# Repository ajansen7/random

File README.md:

# Random Scripts Repository

A collection of various scripts, experiments, and miscellaneous code.

## Projects

### 🧮 Aspens Calculator (`aspens-calculator/`)
- **Purpose**: Computer vision scripts likely for tile or board analysis.
- **Key Tools**: `opencv-python`, `numpy`.
- **Contents**: 
  - Several versions of a calculator (`calc_v*.py`)
  - `training.py` and `training-v2.py` for model training/data collection.
  - `tile-finder.py` for image analysis.

### 🦕 Dino Gen (`dino-gen/`)
- **Purpose**: QR code stitching and image processing, including a Streamlit app.
- **Key Tools**: `streamlit`, `opencv-python`, `pyzbar`.
- **Contents**:
  - `dino_app.py`: Streamlit-based application.
  - `qr_auto_stitch.py`, `qr_manual.py`, `qr_sticter.py`: Tools for QR code processing.

### 🍎 New Fruit (`new-fruit/`)
- **Purpose**: A static web page showcasing fruit/meat hybrids.
- **Key Tools**: HTML, CSS, assets (images and audio).
- **Contents**:
  - `index.html`: The main page.
  - Various image assets like `apple_steak.png` and `banana_sausage.png`.

### 📞 Tattle Phone (`tattle-phone/`)
- **Purpose**: A 3D-printed, toddler-proof 90s-style handset that records "tattles" and uploads them to Google Drive.
- **Key Tools**: ESP32-S3 (Arduino), custom KiCad PCB, Google Apps Script.
- **Contents**:
  - `README.md`: Full design doc (architecture, BOM, power, PCB, enclosure, build plan).
  - `firmware/tattle_phone/`: Record/upload firmware.
  - `cloud/drive_upload.gs`: Drive upload receiver with email notification.

## Setup

### Python Dependencies
To install the necessary Python libraries:

```bash
pip install -r requirements.txt
```

Note: `pyzbar` may require additional system-level libraries (e.g., `libzbar-dev` on Linux or `zbar` via Homebrew on macOS).

## Contributing
Feel free to add your own random scripts or improve existing ones!

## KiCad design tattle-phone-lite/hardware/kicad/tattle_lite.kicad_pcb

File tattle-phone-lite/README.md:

# Tattle Phone Lite

A much cheaper version of [`../tattle-phone`](../tattle-phone): **3 big buttons, 3×AA batteries,
a 2-layer board with every factory part on one side.** Same idea: a toddler presses a button,
it records what they say and sends it to a parent (Google Drive + email), and two phones can
call each other on the home Wi-Fi.

| | Original | Lite |
|---|---|---|
| Buttons | 12-key keypad + CALL | ⭐ TATTLE (yellow star), 🟢 CALL / ANSWER (green circle), 🔴 HANG UP (red square) |
| Lights | 14 smart RGB LEDs | 6 plain LEDs (two per button, matching colours), shining up through holes in the board |
| Power | Li-ion + charger + fuel gauge + buck-boost | 3×AA (alkaline or NiMH) + one 3.3 V regulator; battery level from a resistor divider |
| Board | 4 layers, parts on both sides | 2 layers, factory parts on the back only; you solder the 3 buttons and a few wires |
| Parts per board | ≈ $23 | ≈ $7 |
| Case | 175 × 52–58 × 30 mm | 170 × 60–62 × 34.5 mm, battery door with one screw |

## Status

1. ✅ Parts chosen and checked against JLC stock and datasheets (list below).
2. ✅ Board + case geometry (`hardware/layout.py`), case model (`enclosure/`), STLs build.
3. ✅ KiCad board: 54.4 × 120.5 mm, 2 layers, routed, **DRC 0 errors / 0 unconnected**,
   schematic and board match on all 164 pins. Fab files with a full LCSC BOM in `hardware/fab/`.
4. ✅ Firmware written and **compiles cleanly** (ESP32 core 3.3.12, 0 warnings with `-Wall`). Not yet run on hardware.

## Parts (factory-placed, all on the back)

| Ref | Part | LCSC | Notes |
|---|---|---|---|
| U1 | ESP32-S3-WROOM-1-N8R2 | C2913204 | S3, not C3: the C3 can't decode a PDM mic in hardware and has only one I2S |
| MK1 | LinkMems LMD3526B261-OFA03 | C41347997 | PDM, **bottom port** over a hole in the board. Pins: 1 DATA, 2 L/R, 3 CLK, 4 VDD, 5 GND ring. Do not wash |
| U2 | MAX98357A | C910544 | speaker amp, runs from the batteries |
| U3 | RT9080-33GJ5 | C841192 | 3.3 V LDO, 2 µA idle; same pinout as AP2112K |
| Q1 | AO3401A | C15127 | reverse-battery protection |
| SW4 | Shouhan MSK12C02 | C431540 | power switch, drives the LDO's EN pin only (it's a 50 mA switch) |
| J1 | HRO TYPE-C-31-M-12 | C165948 | **programming only**, no power path: batteries must be in to flash |
| LED1–6 | Lite-On LTST-C230 reverse-mount (yellow C125108, green C125106, red C125107) | | lens fits KiCad's `LED_1206_3216Metric_ReverseMount_Hole1.8x2.4mm` |

**You buy and solder:** see **[SHOPPING.md](SHOPPING.md)** for every part number, the LCSC
order file, the mechanical bits and a from-scratch tool list. The case is sized for a
**Keystone 2465** 3×AA holder (58 × 48.3 × 17 mm); for another holder, measure it and edit
`BATT_HOLDER` in `hardware/layout.py`.

## Case

`enclosure/tattle_lite.scad` (open in OpenSCAD, F5). `cd enclosure && make` builds `stl/` and
`pcb_outline.dxf`; `make renders` makes the pictures in `renders/`.

- **Battery door:** the holder sticks to the inside of the door (foam tape or screws). Undo
  one screw, lift door + holder out on the leads, swap cells. The far end hooks under the back
  wall. A screwed door is the norm for toys for under-3s.
- **Power switch** is recessed in the right side: a fingernail or pen tip moves it, a toddler
  mostly can't.
- **Buttons:** print the caps in translucent filament in each colour. A flange under the
  front wall keeps each one captive once the case is closed.

## Board (`hardware/`)

Everything is generated from two files: `hardware/layout.py` (positions shared with the case)
and `hardware/kicad_gen/design.py` (every part and what each pin connects to).

```
hardware/kicad_gen/run_all.sh     # build -> route -> stitch -> check -> make_fab
```

| Script | Does |
|---|---|
| `build.py` | schematic + placed, unrouted board; writes the mic footprint (from its datasheet), a reverse-mount LED footprint with a slightly smaller lens hole, and a DRC rule for those holes |
| `route.py` | FreeRouting (Java 25 + `~/tools/freerouting/freerouting-2.4.1.jar`). GND is left to the pours; the pours' "plane" blocks are stripped from the DSN so FreeRouting doesn't see a board-sized obstacle. Locked items (the amp's thermal-pad via) are kept |
| `stitch.py` | GND stitching vias on a 4 mm grid wherever both layers have pour, then one via per leftover pour island. Run **once** after `route.py` |
| `check.py` | schematic-vs-board netlist check + grouped DRC |
| `make_fab.py` | Gerbers + drill zip, `bom_jlc.csv` (LCSC numbers from `lcsc.py`), `cpl_jlc.csv` |

`run_all.sh` overwrites the board. Once you've hand-edited it in KiCad, run only `check.py`
and `make_fab.py`. FreeRouting isn't deterministic, so each full run gives slightly different
traces; the checks are what matter.

**Ordering (JLCPCB):** 2 layers, 1.6 mm, 54.4 × 120.5 mm. Min via **0.3 mm** (every hole is
≥ 0.3 mm: KiCad's ESP32 footprint has 0.2 mm thermal vias, which `build.py` re-drills to 0.3 mm,
because 0.2 mm holes move a 2-layer board into a much pricier class). Via covering: **Plugged**
for factory assembly (there's a via in the amp's thermal pad and 12 in the ESP32's ground pad);
**Tented** (or Untented) is fine if you assemble it yourself; see the note on via-in-pad below.
**Assembly: bottom side only.** Upload `hardware/fab/tattle_lite_gerbers.zip`, then
`bom_jlc.csv` + `cpl_jlc.csv`. In the placement preview check the LEDs, U1–U3, Q1 and the mic.
Board options: no washing / no conformal coating (MEMS mic).

**Expected DRC warnings:** "footprint doesn't match library" for the generated/locked
footprints, and two small silkscreen overlaps.

**Assembling it yourself:** stencil + paste + hotplate for the back (one pass), then the three
buttons by hand (clip the leads flush). Hard parts: the mic (no leads, keep paste and air out of
its port, never wash), the amp (3×3 mm QFN), the ESP32's ground pad, USB-C. Vias inside pads
(ESP32 ground pad, amp thermal pad) wick a little solder unless the vias are plugged: use a
touch more paste there or Kapton tape over them on the far side. First power-up from a
current-limited bench supply (~4.5 V, 200 mA) after checking 3V3 and VBAT aren't shorted to GND.

## Firmware (`firmware/tattle_lite/`)

**What the buttons do**

| Button | Idle | Ringing (incoming) | In a call |
|---|---|---|---|
| ⭐ yellow star | record a tattle (beep, talk, it stops on silence or another press) and send it to Drive + email | | |
| 🟢 green circle | call the other phone | answer | (nothing: just talk) |
| 🔴 red square | show battery (3/2/1 red blinks) and go to sleep | decline | hang up (either phone) |

Lights: the button you're using glows (yellow follows your voice while recording; green
follows the other kid's voice in a call). A faint green "breath" when idle means the
phone is on Wi-Fi and can be called.

**Power:** deep sleep until a button is pressed. After any use the phone stays awake
and callable for `AWAKE_MINUTES` (default 5). Optional `PLAY_START_HOUR`/`PLAY_END_HOUR`
keep both phones callable all afternoon (they also wake themselves at the start time),
at the cost of battery: roughly 20-30 mA while awake.

**Calls:** both phones must be on the same Wi-Fi. They find each other by name with
UDP broadcasts (no IP addresses to configure); `INTERCOM_KEY` must match on both. If
your router has "client/AP isolation" (common on guest networks), turn it off for this
network. If the other phone is asleep, the caller hears a descending "sleepy" tune.
Calls are **full duplex** like a real phone: both kids can talk at once. Each phone runs
Espressif's acoustic echo canceller (ESP-SR, built into the ESP32-S3 core) so its own
earpiece isn't sent back to the other kid as an echo. If a call still echoes or howls
after tuning, `#define CALL_MODE_WALKIE` in `config.h` switches to walkie-talkie calls
(hold green to talk); the firmware also falls back to that by itself if the echo
canceller can't start.

**Set up and flash**

1. Deploy `cloud/drive_upload.gs` as a Google Apps Script web app (steps in its header).
2. `cp firmware/tattle_lite/config.example.h firmware/tattle_lite/config.h` and fill in
   Wi-Fi, the upload URL/token, and the two phone names (swapped on the other phone).
3. Batteries in, power ON, USB-C cable to the computer, then
   `firmware/build.sh /dev/cu.usbmodem*` (find the port with `arduino-cli board list`).
   Arduino IDE instead: board "ESP32S3 Dev Module", Flash Size 8MB, PSRAM "QSPI PSRAM",
   Partition Scheme "Custom" (uses `partitions.csv`), USB CDC On Boot "Enabled".
4. If it won't flash: hold 🟢 green while switching on (that's the BOOT strap), flash,
   switch off and on.

**First bring-up, and tuning** (serial monitor at 115200 shows what's happening):
- Recording: `rms=` lines show the mic level. Talking should be well above `SPEECH_RMS`
  (600) and silence well below. Adjust `SPEECH_RMS` / `MIC_GAIN` in `tattle_lite.ino`.
- If the mic reads all zeros, add `#define MIC_RIGHT_SLOT` to `config.h` (some PDM mics
  put "left" data on the other clock edge).
- Battery: the boot line prints the battery voltage; compare with a multimeter.
- Volumes: `TONE_VOLUME`, `RING_VOLUME`, `CALL_VOLUME`.
- Echo (needs both phones): during a call the monitor prints
  `call: mic=… after-aec=… far=…` every 2 s. Have only the *other* kid talk: `after-aec`
  should be far below `mic` (the canceller removing your own earpiece). If it isn't,
  try `CALL_ECHO_DELAY_CHUNKS` 1, 2 or 3 in `config.h`, and keep `CALL_VOLUME` at earpiece
  level. The canceller needs a second or two at the start of each call to lock on.

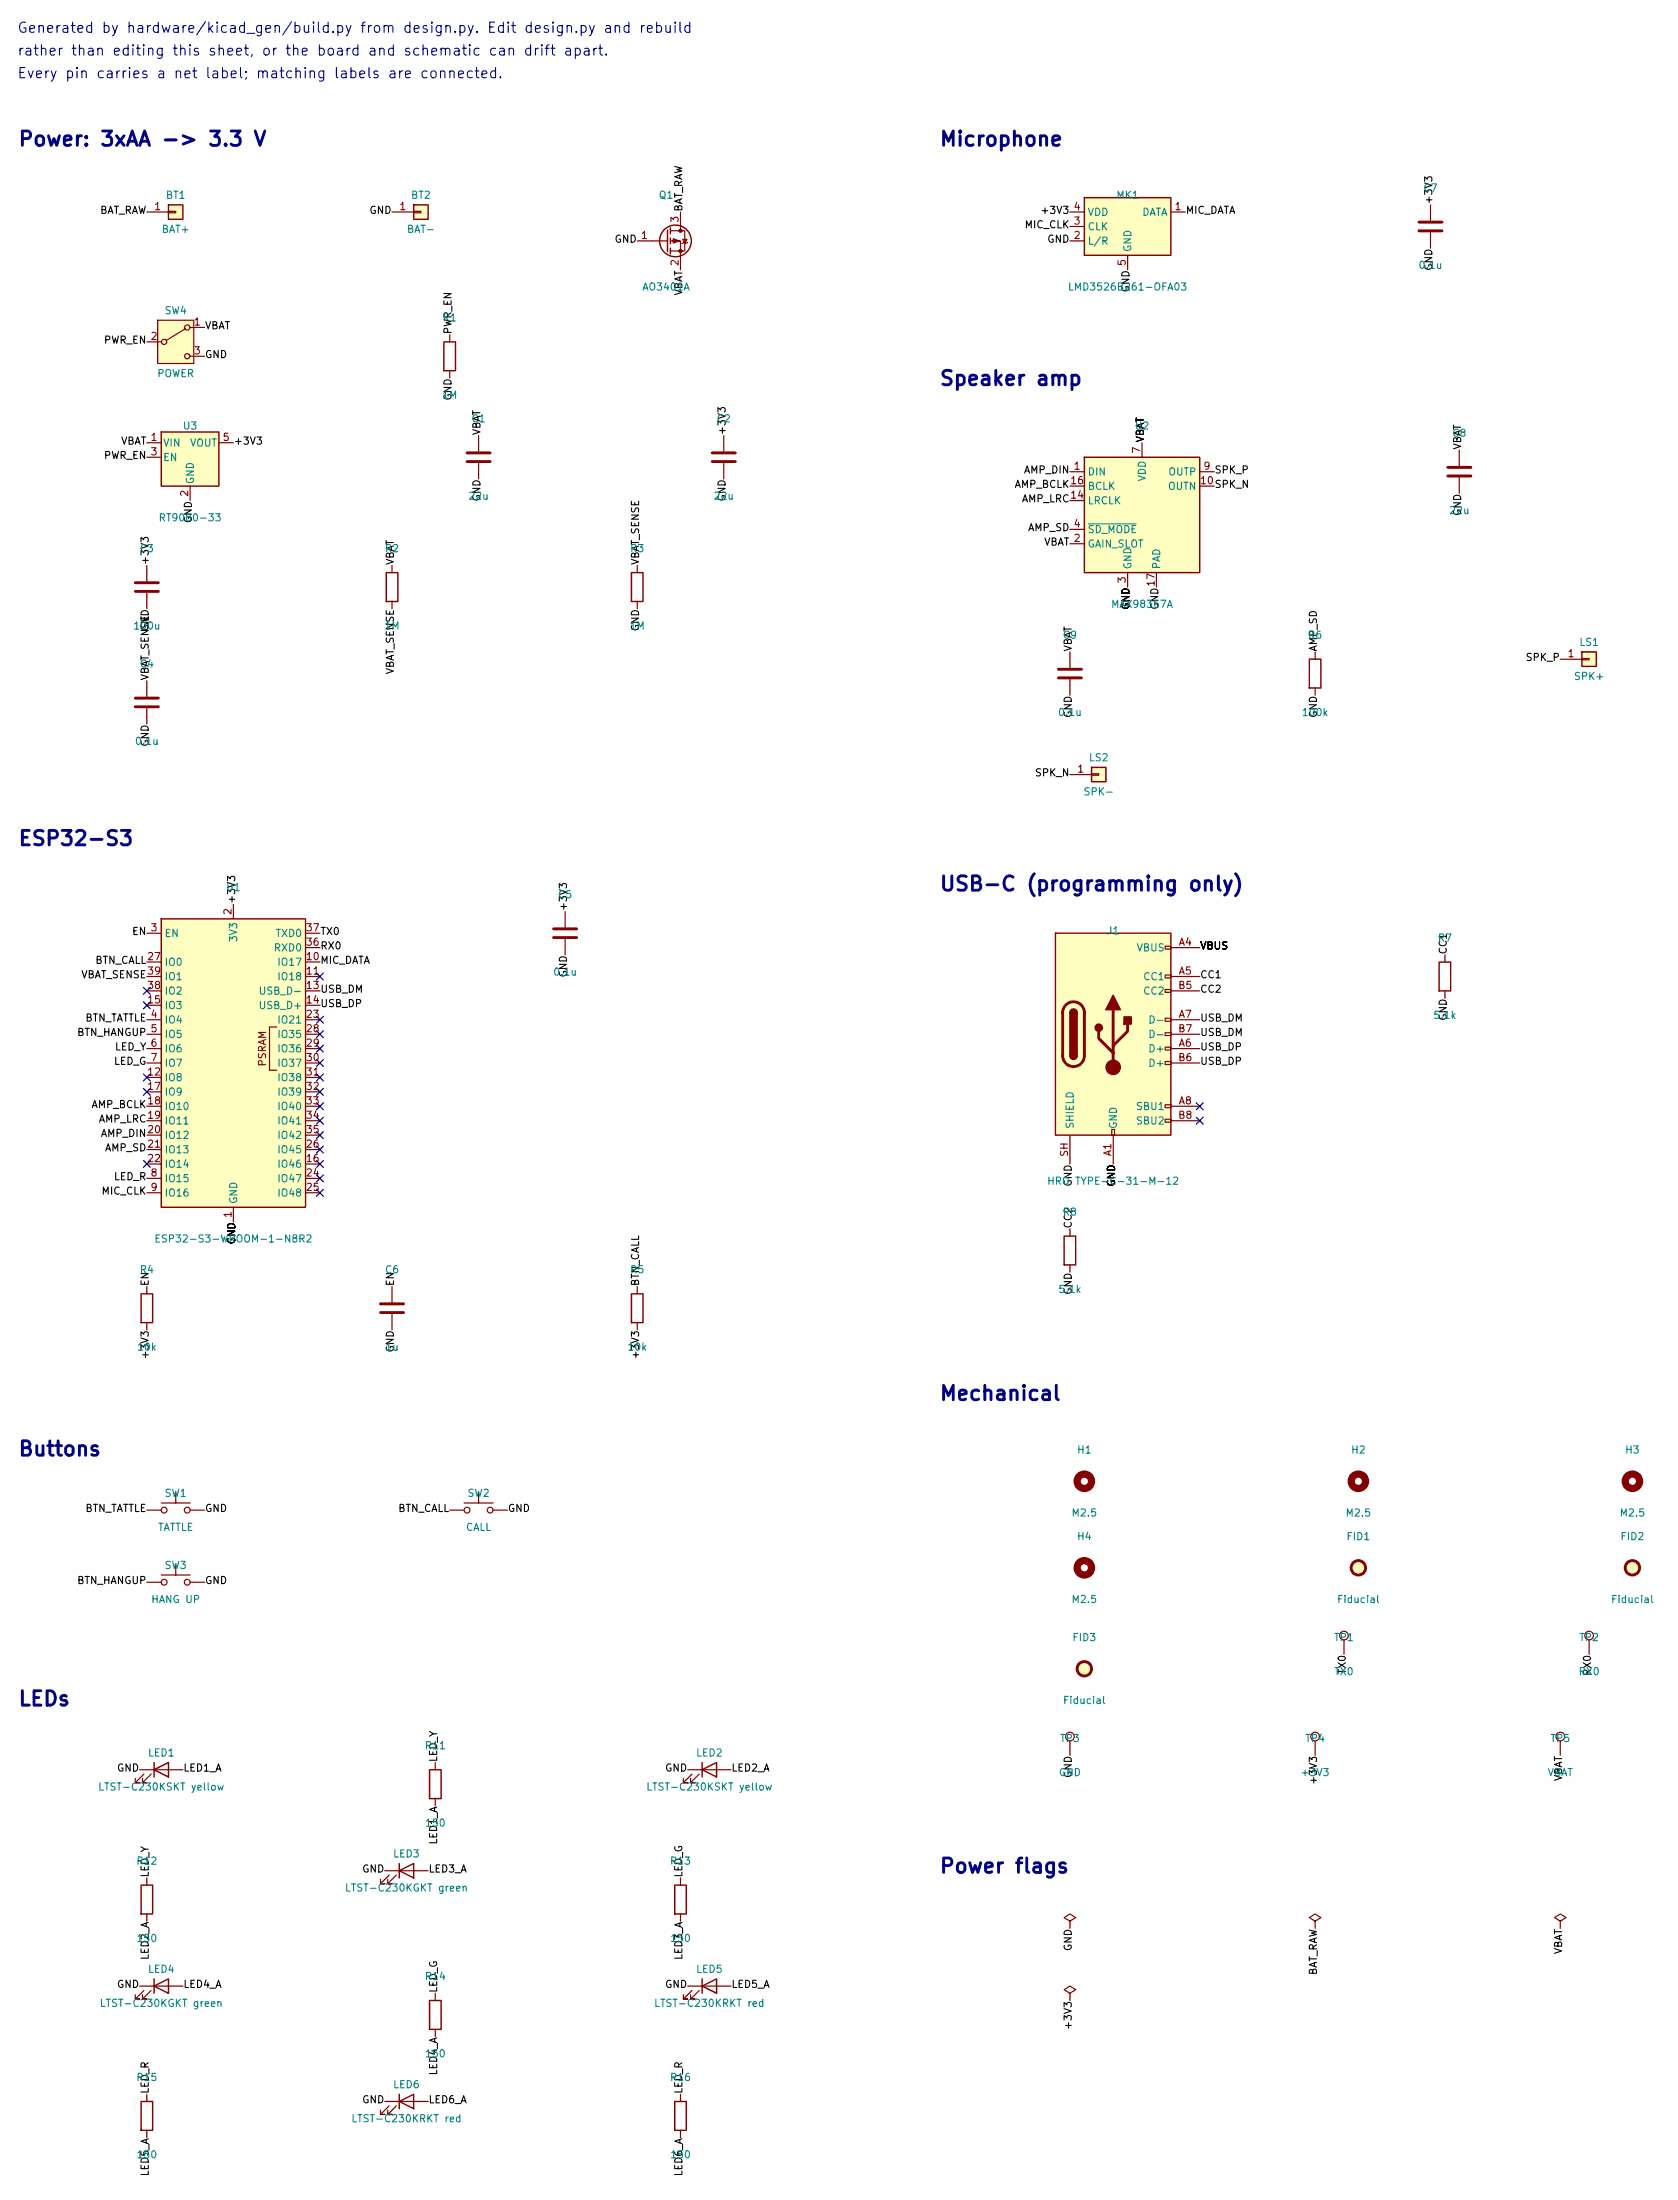
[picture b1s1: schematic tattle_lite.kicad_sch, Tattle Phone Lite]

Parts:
BT1: BAT+; SolderWire-0.5sqmm_1x01_D0.9mm_OD2.1mm
BT2: BAT-; SolderWire-0.5sqmm_1x01_D0.9mm_OD2.1mm
C1, C2, C8: 22u; C_0805_2012Metric
C3: 100u; C_1206_3216Metric
C4, C5, C7, C9: 0.1u; C_0402_1005Metric
C6: 1u; C_0402_1005Metric
FID1, FID2, FID3: Fiducial; Fiducial_1mm_Mask2mm
H1, H2, H3, H4: M2.5; MountingHole_2.7mm_M2.5
J1: HRO TYPE-C-31-M-12; USB_C_Receptacle_HRO_TYPE-C-31-M-12
LED1, LED2: LTST-C230KSKT yellow; LED_1206_3216Metric_ReverseMount_Hole1.65x2.4mm
LED3, LED4: LTST-C230KGKT green; LED_1206_3216Metric_ReverseMount_Hole1.65x2.4mm
LED5, LED6: LTST-C230KRKT red; LED_1206_3216Metric_ReverseMount_Hole1.65x2.4mm
LS1: SPK+; SolderWire-0.5sqmm_1x01_D0.9mm_OD2.1mm
LS2: SPK-; SolderWire-0.5sqmm_1x01_D0.9mm_OD2.1mm
MK1: LMD3526B261-OFA03; LinkMems_LMD3526B261_3.5x2.65mm
Q1: AO3401A; SOT-23
R1, R2, R3: 1M; R_0402_1005Metric
R4, R5: 10k; R_0402_1005Metric
R6: 100k; R_0402_1005Metric
R7, R8: 5.1k; R_0402_1005Metric
R11, R12, R13, R14, R15, R16: 150; R_0402_1005Metric
SW1: TATTLE; SW_PUSH-12mm
SW2: CALL; SW_PUSH-12mm
SW3: HANG UP; SW_PUSH-12mm
SW4: POWER; SW_SPDT_Shouhan_MSK12C02
TP1: TX0; TestPoint_Pad_D1.0mm
TP2: RX0; TestPoint_Pad_D1.0mm
TP3: GND; TestPoint_Pad_D1.0mm
TP4: +3V3; TestPoint_Pad_D1.0mm
TP5: VBAT; TestPoint_Pad_D1.0mm
U1: ESP32-S3-WROOM-1-N8R2; ESP32-S3-WROOM-1_ThermalVias0.3mm
U2: MAX98357A; TQFN-16-1EP_3x3mm_P0.5mm_EP1.23x1.23mm
U3: RT9080-33; SOT-23-5

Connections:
+3V3: C2.1, C3.1, C5.1, C7.1, MK1.4 (VDD), R4.2, R5.2, TP4.1, U1.2 (3V3), U3.5 (VOUT)
AMP_BCLK: U1.18 (IO10), U2.16 (BCLK)
AMP_DIN: U1.20 (IO12), U2.1 (DIN)
AMP_LRC: U1.19 (IO11), U2.14 (LRCLK)
AMP_SD: R6.1, U1.21 (IO13), U2.4 (~SD_MODE)
BAT_RAW: BT1.1, Q1.3 (D)
BTN_CALL: R5.1, SW2.1, U1.27 (IO0)
BTN_HANGUP: SW3.1, U1.5 (IO5)
BTN_TATTLE: SW1.1, U1.4 (IO4)
CC1: J1.A5 (CC1), R7.1
CC2: J1.B5 (CC2), R8.1
EN: C6.1, R4.1, U1.3 (EN)
GND: BT2.1, C1.2, C2.2, C3.2, C4.2, C5.2, C6.2, C7.2, C8.2, C9.2, J1.A1 (GND), J1.A12 (GND), J1.B1 (GND), J1.B12 (GND), J1.SH (SHIELD), LED1.1 (K), LED2.1 (K), LED3.1 (K), LED4.1 (K), LED5.1 (K), LED6.1 (K), MK1.2 (L/R), MK1.5 (GND), Q1.1 (G), R1.2, R3.2, R6.2, R7.2, R8.2, SW1.2, SW2.2, SW3.2, SW4.3 (C), TP3.1, U1.1 (GND), U1.40 (GND), U1.41 (GND), U2.3 (GND), U2.11 (GND), U2.15 (GND), U2.17 (PAD), U3.2 (GND)
LED1_A: LED1.2 (A), R11.2
LED2_A: LED2.2 (A), R12.2
LED3_A: LED3.2 (A), R13.2
LED4_A: LED4.2 (A), R14.2
LED5_A: LED5.2 (A), R15.2
LED6_A: LED6.2 (A), R16.2
LED_G: R13.1, R14.1, U1.7 (IO7)
LED_R: R15.1, R16.1, U1.8 (IO15)
LED_Y: R11.1, R12.1, U1.6 (IO6)
MIC_CLK: MK1.3 (CLK), U1.9 (IO16)
MIC_DATA: MK1.1 (DATA), U1.10 (IO17)
PWR_EN: R1.1, SW4.2 (B), U3.3 (EN)
RX0: TP2.1, U1.36 (RXD0)
SPK_N: LS2.1, U2.10 (OUTN)
SPK_P: LS1.1, U2.9 (OUTP)
TX0: TP1.1, U1.37 (TXD0)
USB_DM: J1.A7 (D-), J1.B7 (D-), U1.13 (USB_D-)
USB_DP: J1.A6 (D+), J1.B6 (D+), U1.14 (USB_D+)
VBAT: C1.1, C8.1, C9.1, Q1.2 (S), R2.1, SW4.1 (A), TP5.1, U2.2 (GAIN_SLOT), U2.7 (VDD), U2.8 (VDD), U3.1 (VIN)
VBAT_SENSE: C4.1, R2.2, R3.1, U1.39 (IO1)
VBUS: J1.A4 (VBUS), J1.A9 (VBUS), J1.B4 (VBUS), J1.B9 (VBUS)

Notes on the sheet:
Power: 3xAA -> 3.3 V
ESP32-S3
Buttons
LEDs
Microphone
Speaker amp
USB-C (programming only)
Mechanical
Power flags
Generated by hardware/kicad_gen/build.py from design.py. Edit design.py and rebuild
rather than editing this sheet, or the board and schematic can drift apart.
Every pin carries a net label; matching labels are connected.

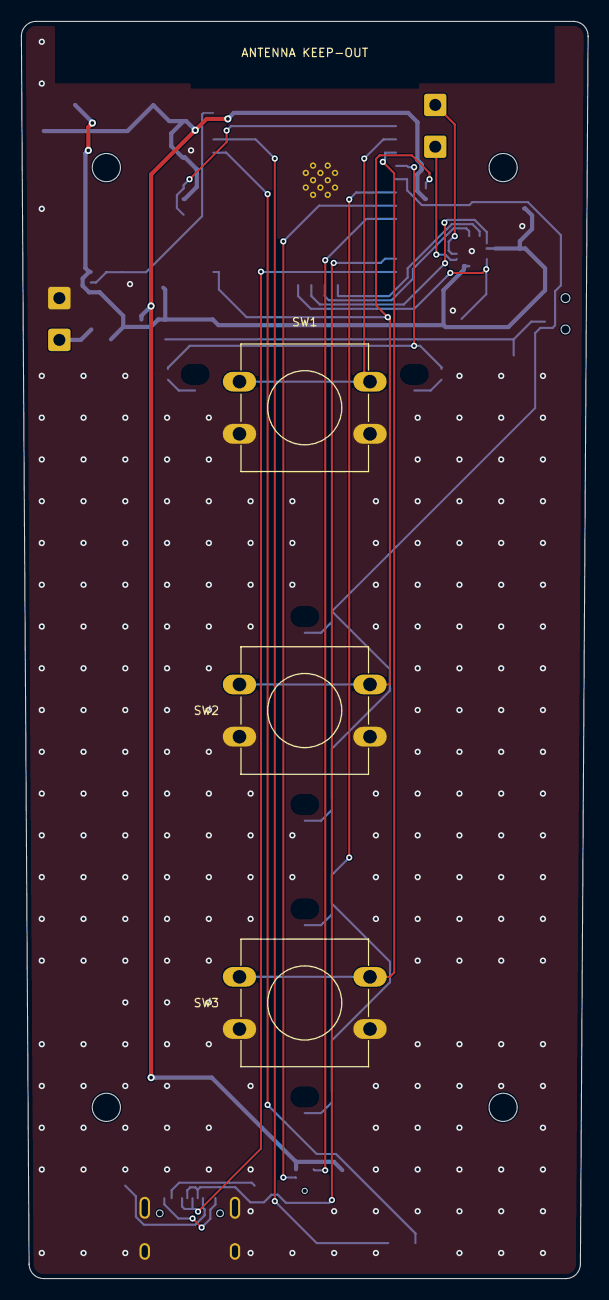
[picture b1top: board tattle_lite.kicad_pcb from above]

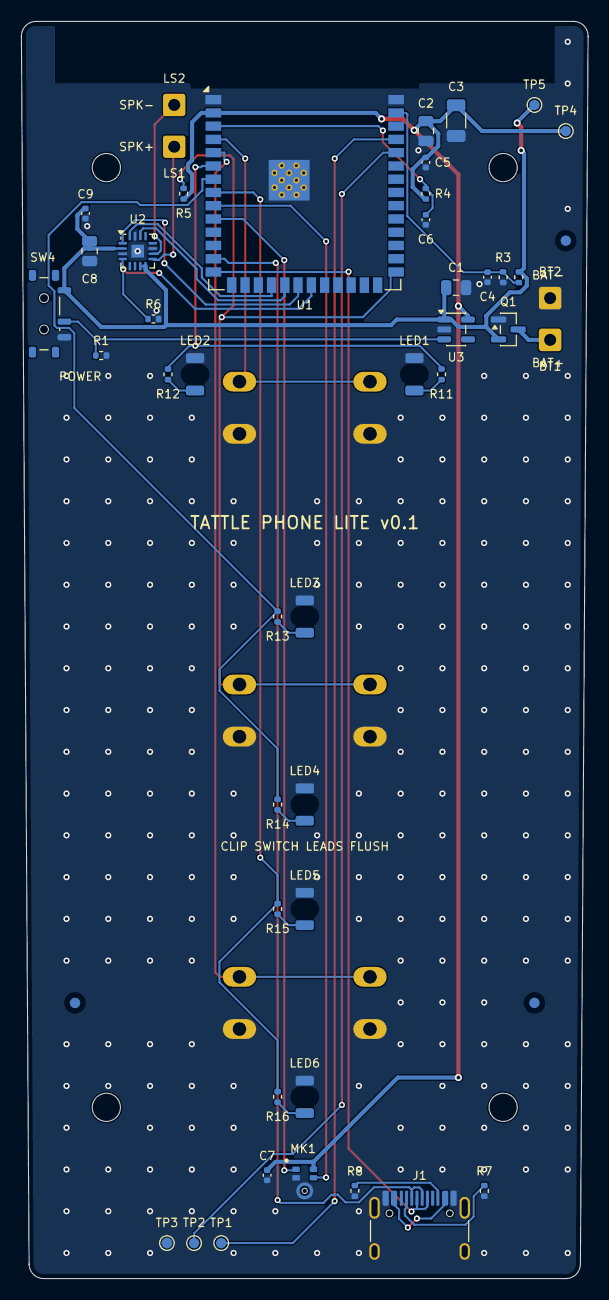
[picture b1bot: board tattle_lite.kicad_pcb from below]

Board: 2 copper layers, 54.3 x 120.4 mm, 55 parts (48 on the bottom side), 34 nets.

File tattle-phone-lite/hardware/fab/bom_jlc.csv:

Comment,Designator,Footprint,LCSC Part #
AO3401A,Q1,SOT-23,C15127
POWER,SW4,SW_SPDT_Shouhan_MSK12C02,C431540
1M,"R1,R2,R3",R_0402_1005Metric,C26083
RT9080-33,U3,SOT-23-5,C841192
22u,"C1,C2,C8",C_0805_2012Metric,C45783
100u,C3,C_1206_3216Metric,C15008
0.1u,"C4,C5,C7,C9",C_0402_1005Metric,C1525
ESP32-S3-WROOM-1-N8R2,U1,ESP32-S3-WROOM-1_ThermalVias0.3mm,C2913204
10k,"R4,R5",R_0402_1005Metric,C25744
1u,C6,C_0402_1005Metric,C52923
LTST-C230KSKT yellow,"LED1,LED2",LED_1206_3216Metric_ReverseMount_Hole1.65x2.4mm,C125108
150,"R11,R12,R13,R14,R15,R16",R_0402_1005Metric,C25082
LTST-C230KGKT green,"LED3,LED4",LED_1206_3216Metric_ReverseMount_Hole1.65x2.4mm,C125106
LTST-C230KRKT red,"LED5,LED6",LED_1206_3216Metric_ReverseMount_Hole1.65x2.4mm,C125107
LMD3526B261-OFA03,MK1,LinkMems_LMD3526B261_3.5x2.65mm,C41347997
MAX98357A,U2,TQFN-16-1EP_3x3mm_P0.5mm_EP1.23x1.23mm,C910544
100k,R6,R_0402_1005Metric,C25741
HRO TYPE-C-31-M-12,J1,USB_C_Receptacle_HRO_TYPE-C-31-M-12,C165948
5.1k,"R7,R8",R_0402_1005Metric,C25905
